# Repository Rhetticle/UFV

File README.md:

# UFV (Unmanned FireFighting Vehicle)
Unmanned firefighting vehicle as part of UQ's ENGG1100 group project course. The group I was a part of (Team White) was awarded first place for achieving a demonstration score of 19.6/20.

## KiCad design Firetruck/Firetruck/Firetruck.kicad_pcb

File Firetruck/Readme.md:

# Receiver

This PCB was mounted inside the cabin of the UFV an listened for data to be sent by the controller. On receiving the joystick positions, the Arduino Nano set the correct PWM signal to the motor drivers in order to move the
wheels/nozzle motors in the correct direction with the correct speed. The PCB was designed in Kicad and manufactured by JLCPCB.

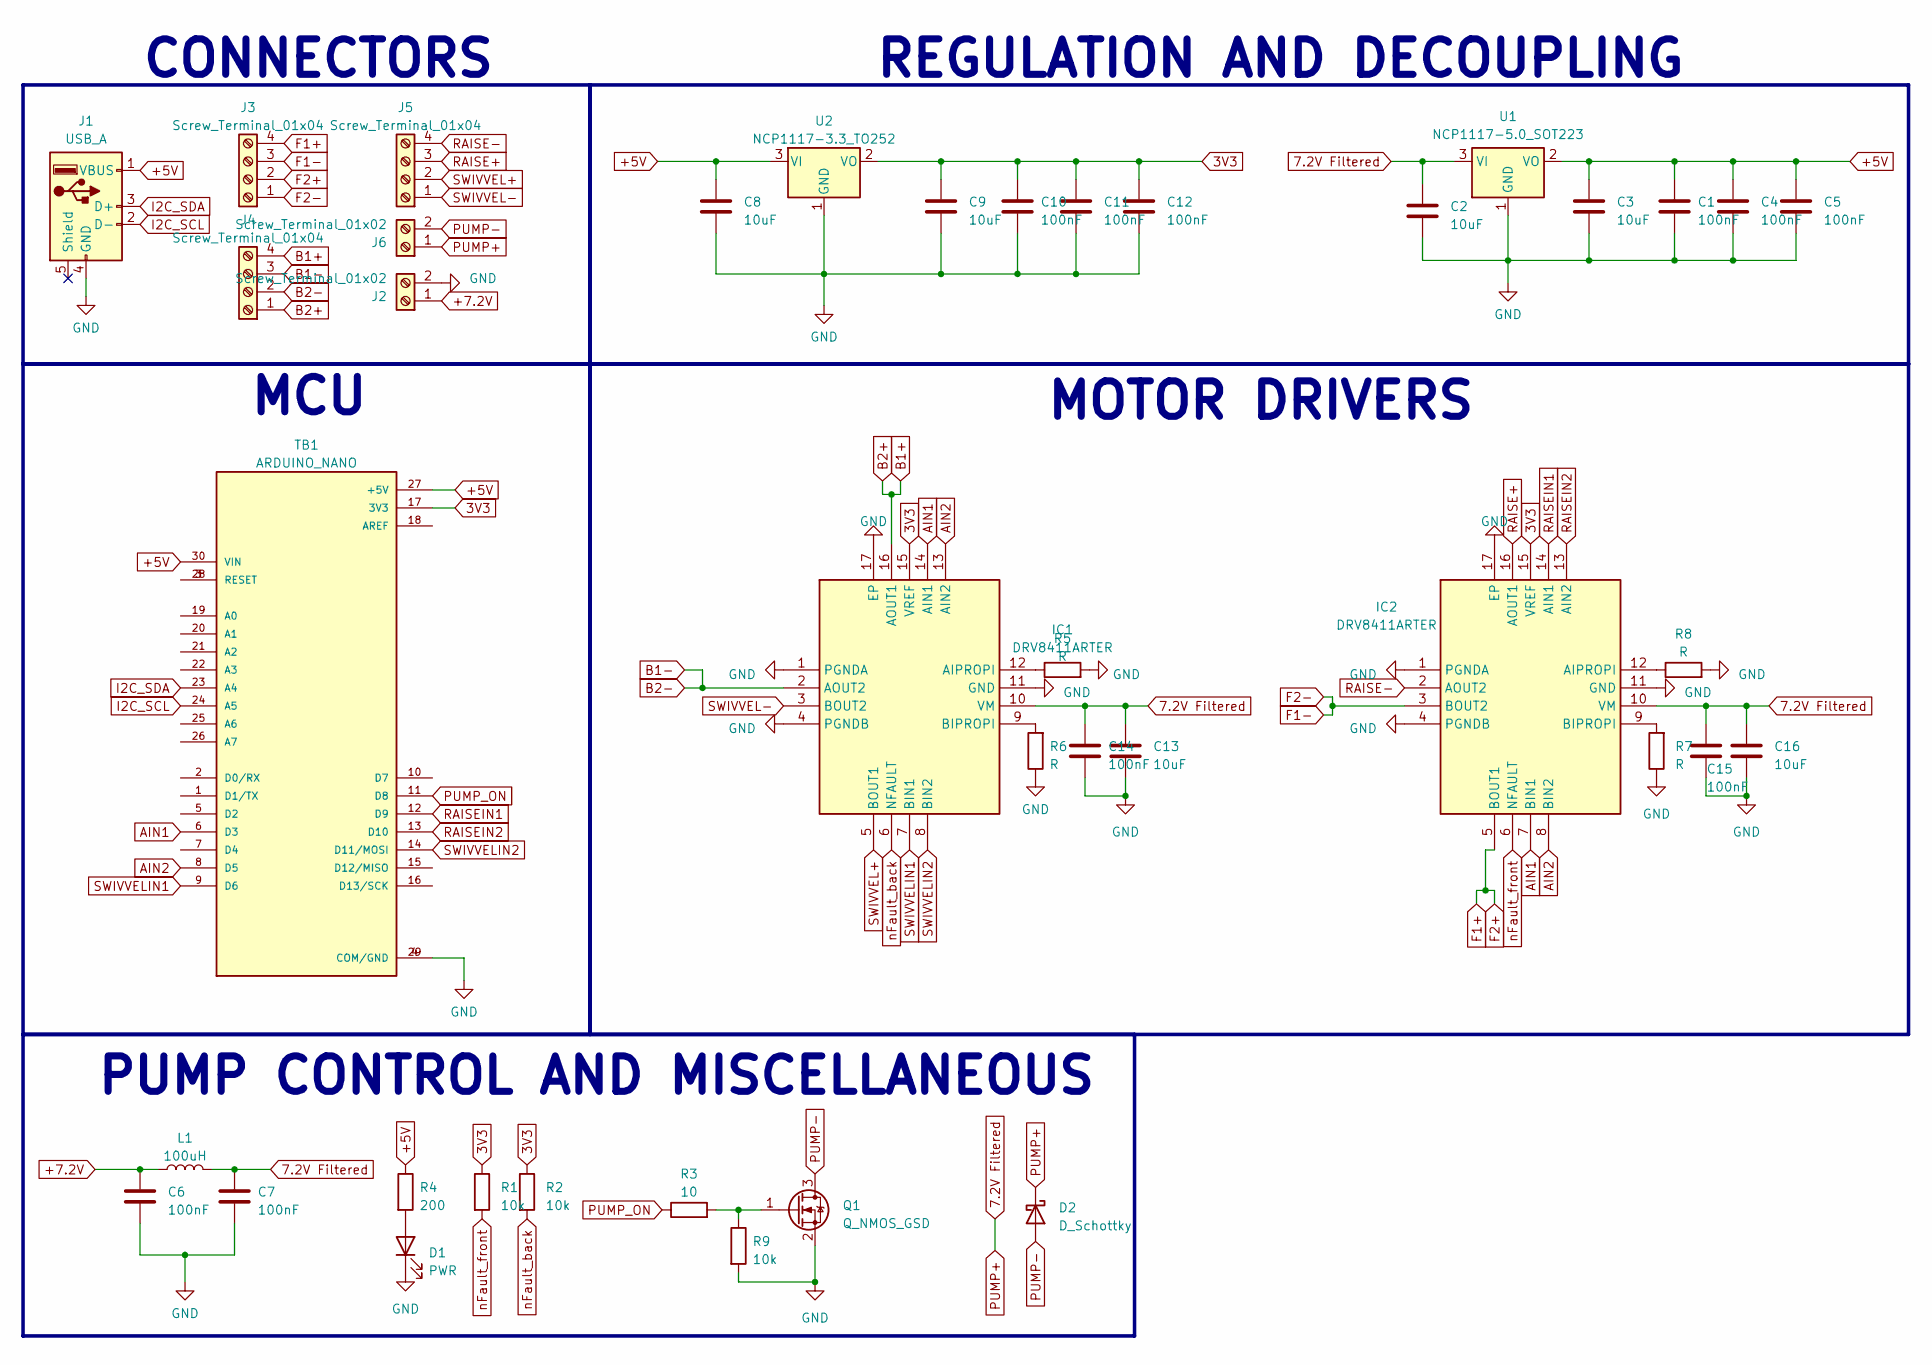
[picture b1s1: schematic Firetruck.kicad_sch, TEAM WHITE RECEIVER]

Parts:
C1, C4, C5, C6, C7, C10, C11, C12, C14, C15: 100nF; C_0603_1608Metric
C2, C3, C9, C13, C16: 10uF; C_0805_2012Metric
C8: 10uF; C_0603_1608Metric
D1: PWR; LED_0603_1608Metric
D2: D_Schottky; D_SOD-123
IC1, IC2: DRV8411ARTER; QFN50P300X300X80-17N-D; Manufacturer_Part_Number DRV8411ARTER; Mouser Part Number 595-DRV8411ARTER
J1: USB_A; USB-2.0-TYPE-A
J2: Screw_Terminal_01x02; JST_VH_B2PS-VH_1x02_P3.96mm_Horizontal
J3, J4, J5: Screw_Terminal_01x04; JST_PH_S4B-PH-K_1x04_P2.00mm_Horizontal
J6: Screw_Terminal_01x02; JST_PH_S2B-PH-K_1x02_P2.00mm_Horizontal
L1: 100uH; L_1210_3225Metric
Q1: Q_NMOS_GSD; SOT-323_SC-70_Handsoldering
R1, R2, R9: 10k; R_0603_1608Metric
R3: 10; R_0603_1608Metric
R4: 200; R_0603_1608Metric
R5, R6, R7, R8: R; R_0603_1608Metric
TB1: ARDUINO_NANO; SHIELD_ARDUINO_NANO
U1: NCP1117-5.0_SOT223; SOT-223-3_TabPin2
U2: NCP1117-3.3_TO252; TO-252-2

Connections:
3V3: C9.1, C10.1, C11.1, C12.1, IC1.15 (VREF), IC2.15 (VREF), R1.1, R2.1, TB1.17 (3V3), U2.2 (VO)
7.2V Filtered: C2.1, C7.1, C13.1, C14.1, C15.1, C16.1, D2.1 (K), IC1.10 (VM), IC2.10 (VM), J6.1, L1.2, U1.3 (VI); also elsewhere on the board
+5V: C1.1, C3.1, C4.1, C5.1, C8.1, J1.1 (VBUS), R4.1, TB1.27 (+5V), TB1.30 (VIN), U1.2 (VO), U2.3 (VI)
+7.2V: C6.1, J2.1, L1.1
AIN1: IC1.14 (AIN1), IC2.7 (BIN1), TB1.6 (D3)
AIN2: IC1.13 (AIN2), IC2.8 (BIN2), TB1.8 (D5)
B1+: IC1.16 (AOUT1), J4.1, J4.4
B1-: IC1.2 (AOUT2), J4.2, J4.3
F1+: IC2.5 (BOUT1), J3.2, J3.4
F1-: IC2.3 (BOUT2), J3.1, J3.3
GND: C1.2, C2.2, C3.2, C4.2, C5.2, C6.2, C7.2, C8.2, C9.2, C10.2, C11.2, C12.2, C13.2, C14.2, C15.2, C16.2, D1.1 (K), IC1.1 (PGNDA), IC1.4 (PGNDB), IC1.11 (GND), IC1.17 (EP), IC2.1 (PGNDA), IC2.4 (PGNDB), IC2.11 (GND), IC2.17 (EP), J1.4 (GND), J2.2, Q1.2 (S), R5.2, R6.1, R7.1, R8.2, R9.2, TB1.4 (COM/GND), TB1.29 (COM/GND), U1.1 (GND), U2.1 (GND); also elsewhere on the board
I2C_SCL: J1.2 (D-), TB1.24 (A5)
I2C_SDA: J1.3 (D+), TB1.23 (A4)
unnamed: D1.2 (A), R4.2
unnamed: IC1.12 (AIPROPI), R5.1
unnamed: IC1.9 (BIPROPI), R6.2
unnamed: IC2.12 (AIPROPI), R8.1
unnamed: IC2.9 (BIPROPI), R7.2
unnamed: Q1.1 (G), R3.2, R9.1
unnamed: TB1.3 (RESET), TB1.28 (RESET)
PUMP-: D2.2 (A), J6.2, Q1.3 (D)
PUMP_ON: R3.1, TB1.11 (D8)
RAISE+: IC2.16 (AOUT1), J5.3
RAISE-: IC2.2 (AOUT2), J5.4
RAISEIN1: IC2.14 (AIN1), TB1.12 (D9)
RAISEIN2: IC2.13 (AIN2), TB1.13 (D10)
SWIVVEL+: IC1.5 (BOUT1), J5.2
SWIVVEL-: IC1.3 (BOUT2), J5.1
SWIVVELIN1: IC1.7 (BIN1), TB1.9 (D6)
SWIVVELIN2: IC1.8 (BIN2), TB1.14 (D11/MOSI)
nFault_back: IC1.6 (NFAULT), R2.2
nFault_front: IC2.6 (NFAULT), R1.2

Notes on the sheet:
MOTOR DRIVERS
REGULATION AND DECOUPLING
CONNECTORS
PUMP CONTROL AND MISCELLANEOUS
MCU

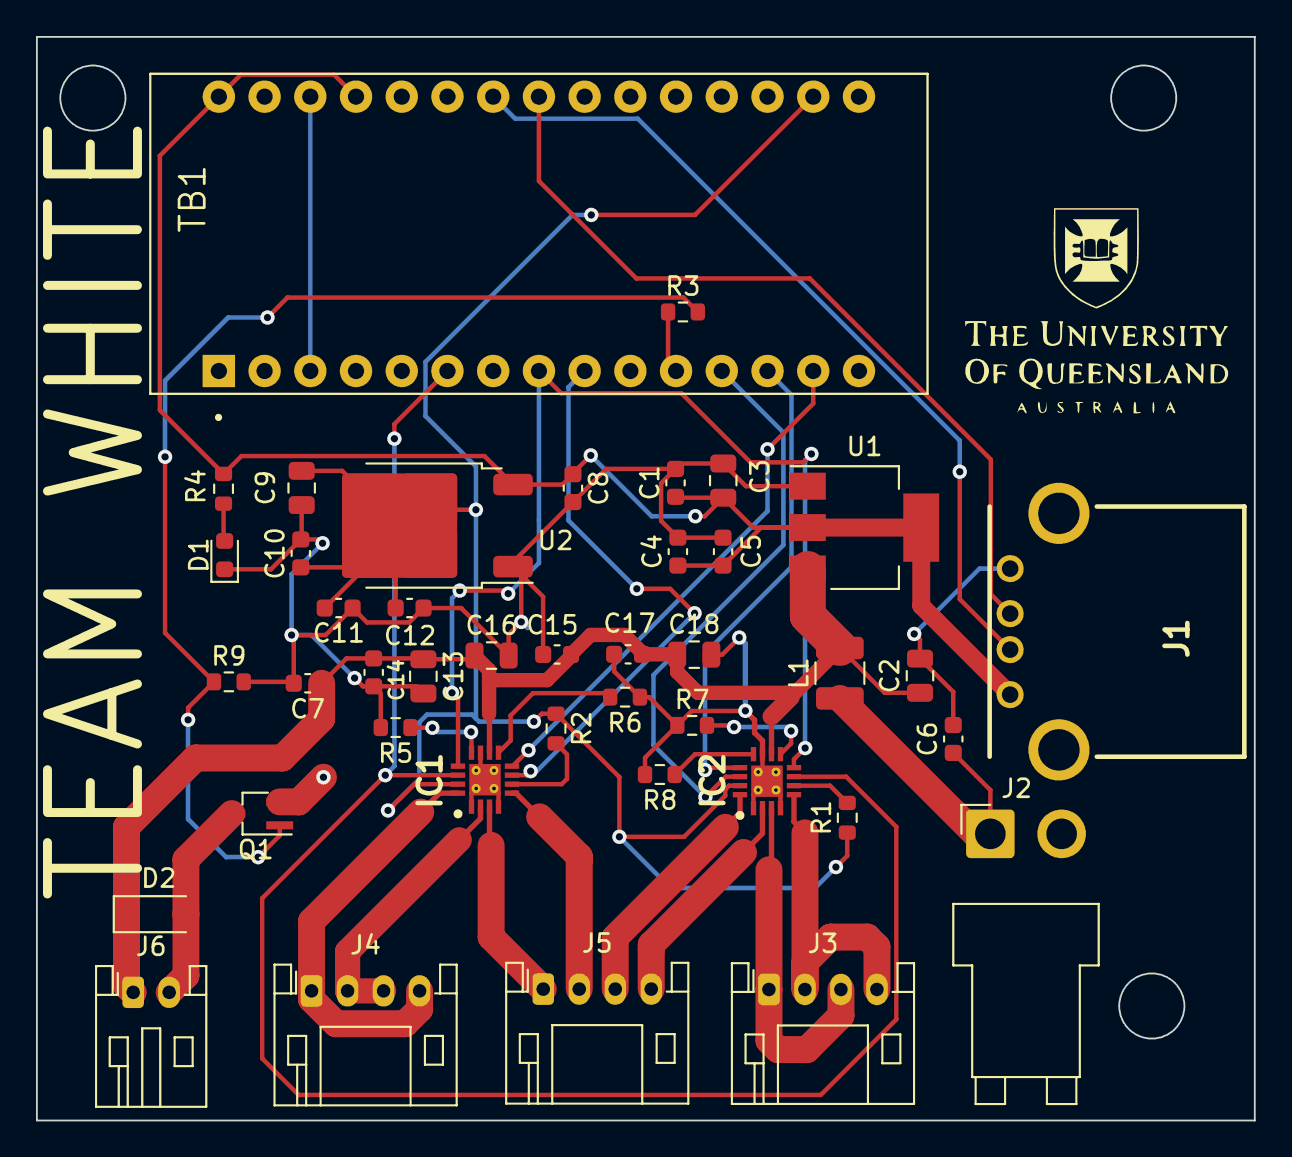
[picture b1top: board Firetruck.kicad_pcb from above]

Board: 2 copper layers, 67.7 x 60.2 mm, 42 parts (0 on the bottom side), 32 nets.

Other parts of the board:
C17: 100nF; C_0603_1608Metric
C18: 10uF; C_0805_2012Metric

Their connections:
7.2V Filtered: C17.1, C18.1; also elsewhere on the board
GND: C17.2, C18.2; also elsewhere on the board

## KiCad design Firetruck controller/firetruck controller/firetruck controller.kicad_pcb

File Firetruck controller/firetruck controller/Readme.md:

# Controller

The controller was used to control the UFV's forward/backward movement as well as the nozzle yaw and pitch and the pump. The controller PCB uses and STM32Gxx microcontroller to monitor joystick positions and transmits this out via I2C
through a standard USB cable where D-/D+ lines are used for SDA and SCL. On power up, the controller sends a random string of characters to the receiving board mounted on the UFV and waits for them to be echoed back as a form of
communication integrity/error checking.

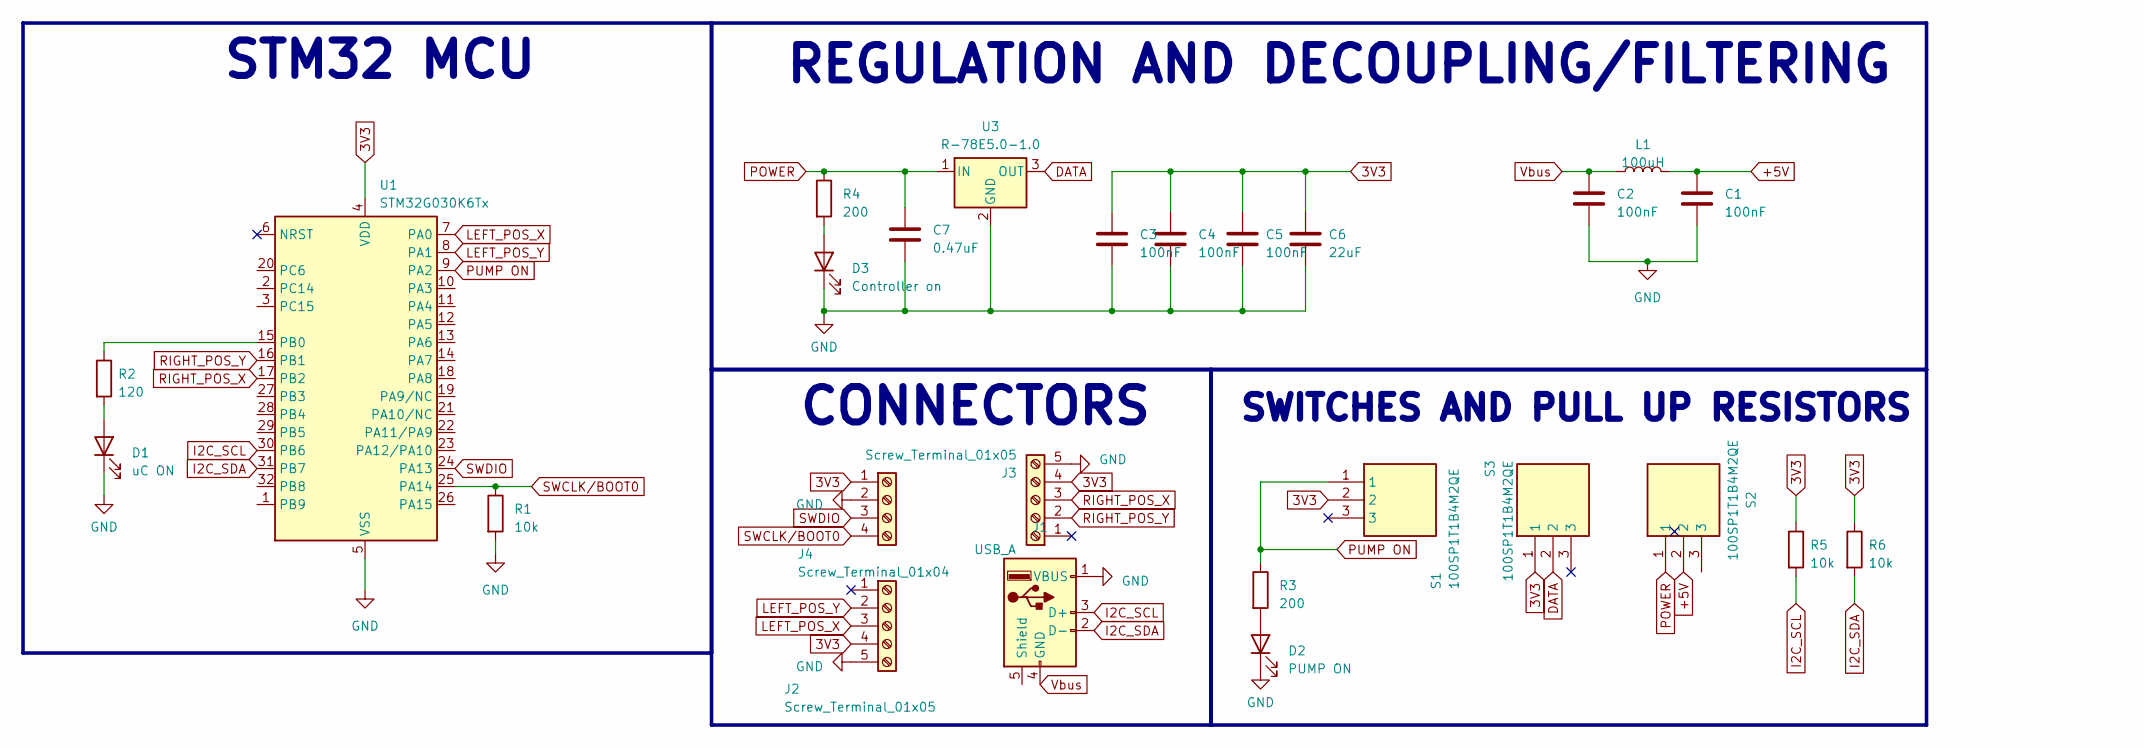
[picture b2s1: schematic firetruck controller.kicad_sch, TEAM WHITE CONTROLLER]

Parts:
C1, C2, C3, C4, C5: 100nF; C_0603_1608Metric
C6: 22uF; C_0805_2012Metric
C7: 0.47uF; C_0603_1608Metric
D1: uC ON; LED_D5.0mm
D2: PUMP ON; LED_D5.0mm
D3: Controller on; LED_D5.0mm
J1: USB_A; USB-2.0-TYPE-A
J2, J3: Screw_Terminal_01x05; PinSocket_1x05_P2.54mm_Horizontal
J4: Screw_Terminal_01x04; PinHeader_1x04_P2.54mm_Horizontal
L1: 100uH; L_1210_3225Metric
R1, R5, R6: 10k; R_0603_1608Metric
R2: 120; R_0603_1608Metric
R3, R4: 200; R_0603_1608Metric
S1, S2, S3: 100SP1T1B4M2QE; Manufacturer_Part_Number 100SP1T1B4M2QE; Mouser Part Number 612-100-A1421
U1: STM32G030K6Tx; LQFP-32_7x7mm_P0.8mm
U3: R-78E5.0-1.0; SOT-223

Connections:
3V3: C3.1, C4.1, C5.1, C6.1, J2.4, J3.4, J4.1, R5.1, R6.1, S1.2, S3.1, U1.4 (VDD)
+5V: C1.1, L1.2, S2.2
GND: C1.2, C2.2, C3.2, C4.2, C5.2, C6.2, C7.2, D1.1 (K), D2.1 (K), D3.1 (K), J1.1 (VBUS), J2.5, J3.5, J4.2, R1.2, U1.5 (VSS); also elsewhere on the board
I2C_SCL: J1.3 (D+), R5.2, U1.30 (PB6)
I2C_SDA: J1.2 (D-), R6.2, U1.31 (PB7)
LEFT_POS_X: J2.3, U1.7 (PA0)
LEFT_POS_Y: J2.2, U1.8 (PA1)
unnamed: D1.2 (A), R2.2
unnamed: D2.2 (A), R3.2
unnamed: D3.2 (A), R4.2
unnamed: R2.1, U1.15 (PB0)
unnamed 11: C7.1, R4.1, S2.1; also elsewhere on the board
unnamed 12: S3.2; also elsewhere on the board
PUMP ON: R3.1, S1.1, U1.9 (PA2)
RIGHT_POS_X: J3.3, U1.17 (PB2)
RIGHT_POS_Y: J3.2, U1.16 (PB1)
SWCLK/BOOT0: J4.4, R1.1, U1.25 (PA14)
SWDIO: J4.3, U1.24 (PA13)
Vbus: C2.1, J1.4 (GND), L1.1

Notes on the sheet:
REGULATION AND DECOUPLING/FILTERING
CONNECTORS
SWITCHES AND PULL UP RESISTORS
STM32 MCU

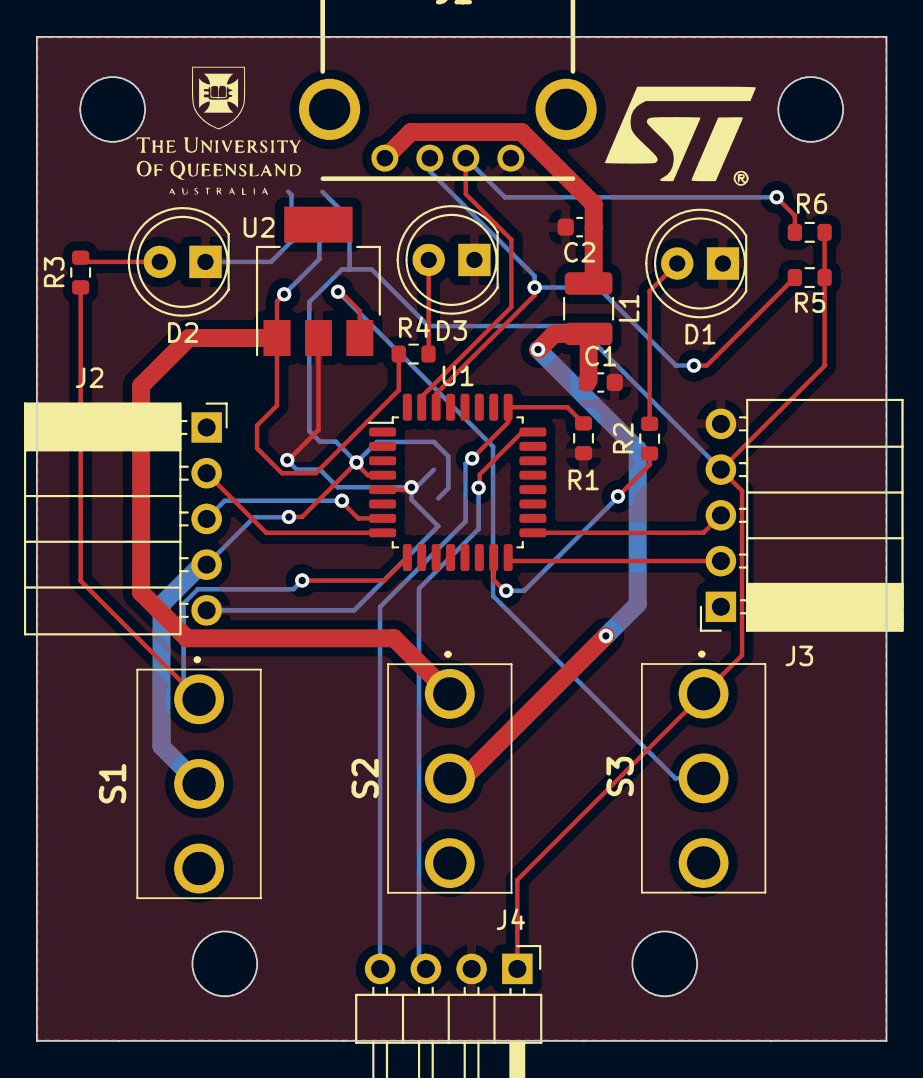
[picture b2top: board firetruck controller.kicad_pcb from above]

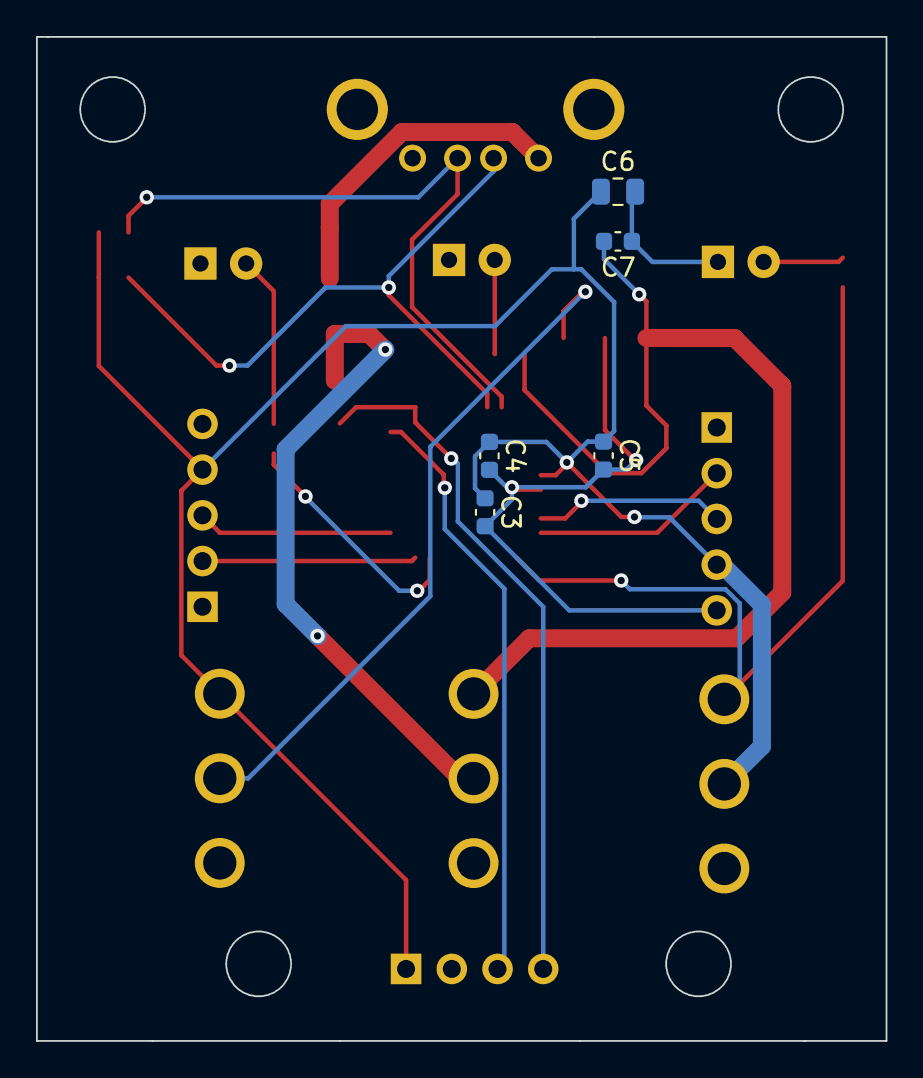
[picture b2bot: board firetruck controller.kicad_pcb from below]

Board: 2 copper layers, 47.2 x 55.8 mm, 26 parts (5 on the bottom side), 19 nets.

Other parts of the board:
U2: R-78E5.0-1.0; SOT-223

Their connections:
GND: U2.2 (GND); also elsewhere on the board
unnamed 11: U2.1 (IN); also elsewhere on the board
unnamed 12: U2.3 (OUT); also elsewhere on the board
